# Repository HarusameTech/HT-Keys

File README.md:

# HT-Keys Public Repository

本リポジトリでは、_HT-Keys_ のファームウェアと開発者向け情報を公開しています

# HT-Keys とは

私 [Harusame](https://twitter.com/HarusameTech) が設計・制作している自作キーボードシリーズです

site：<https://www.harusame.tech/product/keyboard/HT-Keys/>  
購入
- HT-Keys-TKL
  - <https://harusametech.booth.pm/items/4568322>

# 製品シリーズ

## TKL

概要

- US 配列テンキーレス（87 キー）
- USB Type-C インターフェース採用
- CherryMX プロファイル
- RP2040 搭載 Raspberry Pi Pico 互換仕様
- ファームウェアレベルでカスタマイズ可能

## TK

概要

- 独自配列テンキー
- USB Type-C インターフェース採用
- CherryMX プロファイル
- RP2040 搭載 AE-RP2040 使用
- ファームウェアレベルでカスタマイズ可能

# Releases について

本リポジトリでは、以下のような命名規則を使用しています

| Releases の名前 | 意味 |
|:----|:----|
| `Developer Release` | HT-Keys のデバッグや開発用。主に開発者向け |
| `User Release - beta` | HT-Keys の開発段階のファームウェア。主に開発者向け |
| `User Release - Stable` | HT-Keys のファームウェア。使用者向け |

※ファームウェア開発を行うにあたり、何かしらのバグの解消ができたものを `beta` とし、開発時点で見つかっているバグをおおよそ、あるいは全て解消できたものを `Stable` としています

# ご使用の際の注意事項

本キーボードは US 配列です。そのため、Windows のキーボード設定を以下のように変更する必要があります

[設定] -> [言語と時刻] -> [言語] -> [優先する言語] の「オプション」から、ハードウェアキーボードレイアウトを変更してください

<div align="center"></div>
<div align="center">↓</div>
<div align="center"></div>
<div align="center">↓</div>
<div align="center"></div>

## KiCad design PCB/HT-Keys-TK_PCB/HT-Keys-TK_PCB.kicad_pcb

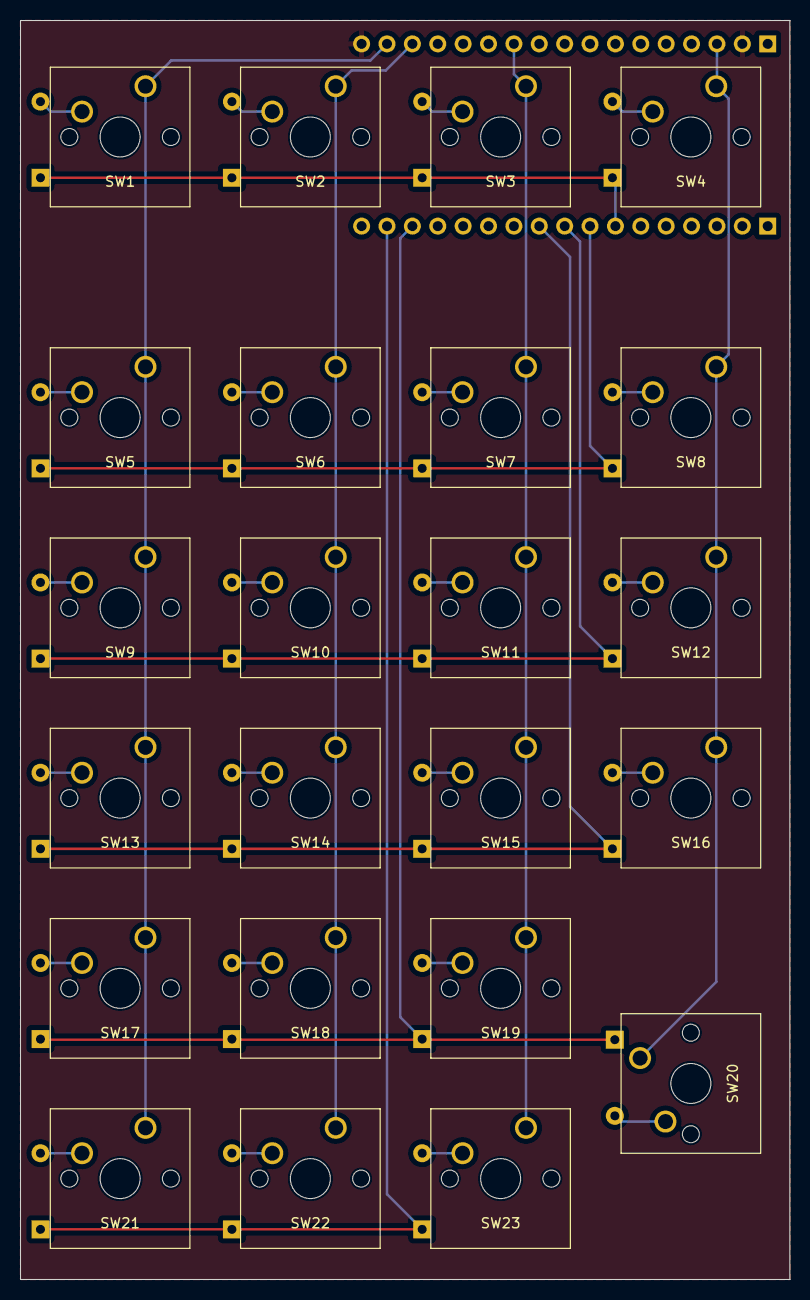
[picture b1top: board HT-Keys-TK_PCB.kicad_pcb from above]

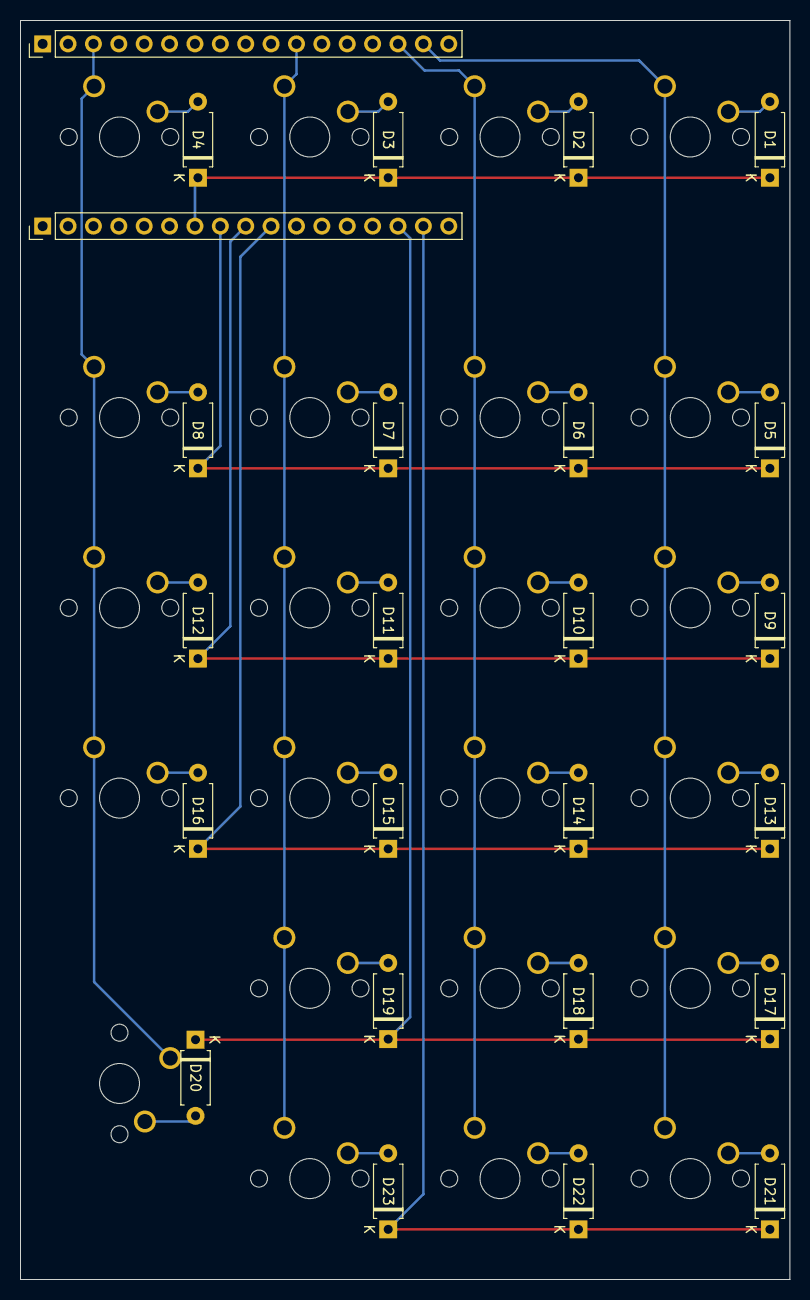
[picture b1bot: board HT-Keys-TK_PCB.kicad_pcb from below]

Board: 2 copper layers, 77.0 x 126.0 mm, 48 parts (25 on the bottom side), 34 nets.

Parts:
D1, D2, D3, D4, D5, D6, D7, D8, D9, D10, D11, D12, D13, D14, D15, D16, D17, D18, D19, D20, D21, D22, D23: D; D_A-405_P7.62mm_Horizontal
J1, J2: Conn_01x17_Pin; PinHeader_1x17_P2.54mm_Vertical
SW1, SW2, SW3, SW4, SW5, SW6, SW7, SW8, SW9, SW10, SW11, SW12, SW13, SW14, SW15, SW16, SW17, SW18, SW19, SW21, SW22, SW23: SW_Push; SW_Cherry_MX_1.00u_PCB
SW20: SW_Push; SW_Cherry_MX_2.00u_PCB

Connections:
GND: J2.2, J2.17
unnamed: D1.2 (A), SW1.2
unnamed: D2.2 (A), SW2.2
unnamed: D3.2 (A), SW3.2
unnamed: D4.2 (A), SW4.2
unnamed: D5.2 (A), SW5.2
unnamed: D6.2 (A), SW6.2
unnamed: D7.2 (A), SW7.2
unnamed: D8.2 (A), SW8.2
unnamed: D9.2 (A), SW9.2
unnamed: D10.2 (A), SW10.2
unnamed: D11.2 (A), SW11.2
unnamed: D12.2 (A), SW12.2
unnamed: D13.2 (A), SW13.2
unnamed: D14.2 (A), SW14.2
unnamed: D15.2 (A), SW15.2
unnamed: D16.2 (A), SW16.2
unnamed: D17.2 (A), SW17.2
unnamed: D18.2 (A), SW18.2
unnamed: D19.2 (A), SW19.2
unnamed: D20.2 (A), SW20.2
unnamed: D21.2 (A), SW21.2
unnamed: D22.2 (A), SW22.2
unnamed: D23.2 (A), SW23.2
Read0: J2.16, SW1.1, SW5.1, SW9.1, SW13.1, SW17.1, SW21.1
Read1: J2.15, SW2.1, SW6.1, SW10.1, SW14.1, SW18.1, SW22.1
Read2: J2.11, SW3.1, SW7.1, SW11.1, SW15.1, SW19.1, SW23.1
Read3: J2.3, SW4.1, SW8.1, SW12.1, SW16.1, SW20.1
Scan0: D1.1 (K), D2.1 (K), D3.1 (K), D4.1 (K), J1.7
Scan1: D5.1 (K), D6.1 (K), D7.1 (K), D8.1 (K), J1.8
Scan2: D9.1 (K), D10.1 (K), D11.1 (K), D12.1 (K), J1.9
Scan3: D13.1 (K), D14.1 (K), D15.1 (K), D16.1 (K), J1.10
Scan4: D17.1 (K), D18.1 (K), D19.1 (K), D20.1 (K), J1.15
Scan5: D21.1 (K), D22.1 (K), D23.1 (K), J1.16

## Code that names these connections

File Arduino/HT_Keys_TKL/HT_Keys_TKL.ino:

/* NOTE
 * If a compile error occurs,
 * Use "Raspberry Pi Pico/RP2040" by Earle F.Philhower
 * instead of "Arduino Mbed OS RP2040 Boards" by Arduino
 */


#include <Keyboard.h>
#define US_KEYBOARD

// キーマトリクスの処理の有効無効を指定:
// #define DEBUG_Matrix

// 実行速度モニタリングの有効無効を指定:
// #define DEBUG_Times

// キー出力を無効にする:
// #define DISABLE_KEYOUT

#ifdef DEBUG_Times
 #ifndef DEBUG
  #define DEBUG
 #endif
#endif

#ifdef DEBUG_Matrix
 #ifndef DEBUG
  #define DEBUG
 #endif
#endif

/* キー出力モードの指定用 */
#define MODE_Press true
#define MODE_Release false

/* 使用するGPIOを定義 */
#define Scan0 25
#define Scan1 20
#define Scan2 19
#define Scan3 18
#define Scan4 17
#define Scan5 16

#define Read0   0
#define Read1   1
#define Read2   2
#define Read3   3
#define Read4   4
#define Read5   5
#define Read6   6
#define Read7   7
#define Read8   8
#define Read9   9
#define Read10 10
#define Read11 11
#define Read12 12
#define Read13 13
#define Read14 21
#define Read15 23
#define Read16 24

/* 各キースイッチとそれに割り当てるキーの対応を定義 */
#define SW1  Key_ESC
#define SW2  Key_F1
#define SW3  Key_F2
#define SW4  Key_F3
#define SW5  Key_F4
#define SW6  Key_F5
#define SW7  Key_F6
#define SW8  Key_F7
#define SW9  Key_F8
#define SW10 Key_F9
#define SW11 Key_F10
#define SW12 Key_F11
#define SW13 Key_F12
#define SW14 Key_PrintScrn
#define SW15 Key_ScrollLock
#define SW16 Key_Pause
#define SW17 Key_Tilde
#define SW18 Key_1
#define SW19 Key_2
#define SW20 Key_3
#define SW21 Key_4
#define SW22 Key_5
#define SW23 Key_6
#define SW24 Key_7
#define SW25 Key_8
#define SW26 Key_9
#define SW27 Key_0
#define SW28 Key_Hyphen
#define SW29 Key_Equal
#define SW30 Key_Backspace
#define SW31 Key_Insert
#define SW32 Key_Home
#define SW33 Key_PageUp
#define SW34 Key_Tab
#define SW35 Key_Q
#define SW36 Key_W
#define SW37 Key_E
#define SW38 Key_R
#define SW39 Key_T
#define SW40 Key_Y
#define SW41 Key_U
#define SW42 Key_I
#define SW43 Key_O
#define SW44 Key_P
#define SW45 Key_L_Bracket
#define SW46 Key_R_Bracket
#define SW47 Key_BackSlash
#define SW48 Key_Delete
#define SW49 Key_End
#define SW50 Key_PageDown
#define SW51 Key_CapsLock
#define SW52 Key_A
#define SW53 Key_S
#define SW54 Key_D
#define SW55 Key_F
#define SW56 Key_G
#define SW57 Key_H
#define SW58 Key_J
#define SW59 Key_K
#define SW60 Key_L
#define SW61 Key_SemiColon
#define SW62 Key_Quote
#define SW63 Key_Enter
#define SW64 Key_L_Shift
#define SW65 Key_Z
#define SW66 Key_X
#define SW67 Key_C
#define SW68 Key_V
#define SW69 Key_B
#define SW70 Key_N
#define SW71 Key_M
#define SW72 Key_camma
#define SW73 Key_period
#define SW74 Key_slash
#define SW75 Key_R_Shift
#define SW76 Key_UP
#define SW77 Key_L_Ctrl
#define SW78 Key_L_Win
#define SW79 Key_L_Alt
#define SW80 Key_Space
#define SW81 Key_R_Alt
#define SW82 Key_R_Win
#define SW83 Key_App
#define SW84 Key_R_Ctrl
#define SW85 Key_LT
#define SW86 Key_DN
#define SW87 Key_RT


/* キー名称とキーコードの対応を定義 */
#define Null            0x00
#define Key_ESC         0xB1
#define Key_F1          0xC2
#define Key_F2          0xC3
#define Key_F3          0xC4
#define Key_F4          0xC5
#define Key_F5          0xC6
#define Key_F6          0xC7
#define Key_F7          0xC8
#define Key_F8          0xC9
#define Key_F9          0xCA
#define Key_F10         0xCB
#define Key_F11         0xCC
#define Key_F12         0xCD
#define Key_PrintScrn   0xCE
#define Key_ScrollLock  0xCF
#define Key_Pause       0xD0
#define Key_Tilde       0x60
#define Key_1           0x31
#define Key_2           0x32
#define Key_3           0x33
#define Key_4           0x34
#define Key_5           0x35
#define Key_6           0x36
#define Key_7           0x37
#define Key_8           0x38
#define Key_9           0x39
#define Key_0           0x30
#define Key_Hyphen      0x2D
#define Key_Equal       0x3D
#define Key_Backspace   0xB2
#define Key_Insert      0xD1
#define Key_Home        0xD2
#define Key_PageUp      0xD3
#define Key_Tab         0xB3
#define Key_Q           0x71
#define Key_W           0x77
#define Key_E           0x65
#define Key_R           0x72
#define Key_T           0x74
#define Key_Y           0x79
#define Key_U           0x75
#define Key_I           0x69
#define Key_O           0x6F
#define Key_P           0x70
#define Key_L_Bracket   0x5B
#define Key_R_Bracket   0x5D
#define Key_BackSlash   0x5C
#define Key_Delete      0xD4
#define Key_End         0xD5
#define Key_PageDown    0xD6
#define Key_CapsLock    0xC1
#define Key_A           0x61
#define Key_S           0x73
#define Key_D           0x64
#define Key_F           0x66
#define Key_G           0x67
#define Key_H           0x68
#define Key_J           0x6A
#define Key_K           0x6B
#define Key_L           0x6C
#define Key_SemiColon   0x3B
#define Key_Quote       0x27
#define Key_Enter       0xB0
#define Key_L_Shift     0x81
#define Key_Z           0x7A
#define Key_X           0x78
#define Key_C           0x63
#define Key_V           0x76
#define Key_B           0x62
#define Key_N           0x6E
#define Key_M           0x6D
#define Key_camma       0x2C
#define Key_period      0x2E
#define Key_slash       0x2F
#define Key_R_Shift     0x85
#define Key_UP          0xDA
#define Key_L_Ctrl      0x80
#define Key_L_Win       0x83
#define Key_L_Alt       0x82
#define Key_Space       0x20
#define Key_R_Alt       0x86
#define Key_R_Win       0x87
#define Key_App         0xED
#define Key_R_Ctrl      0x84
#define Key_LT          0xD8
#define Key_DN          0xD9
#define Key_RT          0xD7

/* GPIO初期化用配列 */
const uint8_t Scan[] = {Scan0, Scan1, Scan2, Scan3, Scan4, Scan5 };
const uint8_t Read[] = {Read0, Read1, Read2, Read3, Read4, Read5, Read6, Read7, Read8, Read9, Read10, Read11, Read12, Read13, Read14, Read15, Read16};

/* キーマトリクス操作用配列 */
const uint8_t keyMap[sizeof(Scan)][sizeof(Read)] = {
  {SW1 , Null, SW2 , SW3 , SW4 , SW5 , SW6 , SW7 , SW8 , SW9 , SW10, SW11, SW12, SW13, SW14, SW15, SW16},
  {SW17, SW18, SW19, SW20, SW21, SW22, SW23, SW24, SW25, SW26, SW27, SW28, SW29, SW30, SW31, SW32, SW33},
  {SW34, SW35, SW36, SW37, SW38, SW39, SW40, SW41, SW42, SW43, SW44, SW45, SW46, SW47, SW48, SW49, SW50},
  {SW51, SW52, SW53, SW54, SW55, SW56, SW57, SW58, SW59, SW60, SW61, SW62, Null, SW63, Null, Null, Null},
  {SW64, SW65, SW66, SW67, SW68, SW69, SW70, SW71, SW72, SW73, SW74, Null, Null, SW75, Null, SW76, Null},
  {SW77, SW78, SW79, Null, Null, SW80, Null, Null, Null, SW81, SW82, SW83, Null, SW84, SW85, SW86, SW87}};

/* キーマトリクスの状態保存用配列 */
volatile uint8_t Matrix[sizeof(Scan)][sizeof(Read)];

void setup() {
#ifdef DEBUG
  /* デバッグ用シリアル通信を115200bpsで開始 */
  Serial.begin(115200);
#endif

  /* 読み取り線を入力にしてプルアップ */
  for(uint8_t i = 0; i < sizeof(Read); i++) {
    pinMode(Read[i], INPUT_PULLUP);
  }

  /* スキャン線を出力にしてすべてHIGH */
  for(uint8_t i = 0; i < sizeof(Scan); i++) {
    pinMode(Scan[i], OUTPUT);
    digitalWrite(Scan[i], HIGH);
  }
 
#ifndef DISABLE_KEYOUT
  /* キーボードエミュレート開始 */
  Keyboard.begin();
#endif
}

void loop() {
  readKeyPad();  // キーボードの状態を読み取り、配列を更新する:
  checkMatrix();  // 配列を参照し押されたかどうかを判断:

  delayMicroseconds(4000);
}

void readKeyPad(void) {
  for(uint8_t i = 0; i < sizeof(Scan); i++) {     // スキャン線を順に切り替え:
    digitalWrite(Scan[i], LOW);                   // 読み取るところだけ落とす:
    delayMicroseconds(8);                         // ゴースト発生防止:
    for(uint8_t o = 0; o < sizeof(Read); o++) {   // 読み取って配列を更新:
      Matrix[i][o] = (Matrix[i][o] << 1) + (digitalRead(Read[o]) ? 0 : 1);
      delayMicroseconds(8);                       // ゴースト発生防止:
    }
    digitalWrite(Scan[i], HIGH);                  // 定常状態に戻す:
  }

#ifdef DEBUG_Matrix
  /* デバッグ表示 */
  for(uint8_t i = 0; i < sizeof(Scan); i++) {
    Serial.print(" | ");
    for(uint8_t o = 0; o < sizeof(Read); o++) {
      for(uint8_t b = 7; b > 0; b--) {            // 配列のデータを MSB から選択:
        if((Matrix[i][o] & 1 << b) == 0) {        // 配列のデータの対応するビットが 0 かどうかを判定:
          Serial.print("0");
        }else {
          Serial.print("1");
        }
      }
      Serial.print(" | ");
    }
    Serial.print("\n");
  }
  Serial.print("\n");
#endif
}

void checkMatrix(void) {
  /* キーボード出力 */
  for(uint8_t i = 0; i < sizeof(Scan); i++) {
    for(uint8_t o = 0; o < sizeof(Read); o++) {
      if((Matrix[i][o] & 0b00001111) == 0b00000011) {
        keyOut(keyMap[i][o], MODE_Press);
      }else if((Matrix[i][o] & 0b00000111) == 0b00000100) {
        keyOut(keyMap[i][o], MODE_Release);
      }
    }
  }
}

void keyOut(const uint8_t key, const bool mode) {
#ifndef DISABLE_KEYOUT
  if(key == 0) {
  }else {
    if(mode) {
      Keyboard.press(key);
    }else {
      Keyboard.release(key);
    }
  }
#endif
}

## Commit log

2023-03-06 Update HT_Keys_TKL.ino
    バックスラッシュキー以外のキーコードの特定が完了
2023-03-07 Update HT_Keys_TKL.ino
    US 配列を明示するように変更
    大文字が入力されていたので小文字になるように `0x20` を引くように変更
    バージョン番号をコード内に追加
2023-03-09 Add files via upload
    回路図の PDF ファイルを追加
2023-05-05 fix fqbn
2023-05-05 fix path
2023-05-06 fix build.yaml
2023-05-06 edit build.yaml
2023-07-07 シフトキーのキーコードを修正
2023-07-08 シフトキーを入れ替え
2023-07-15 不要なルーチンを削除
2023-07-15 キーリリースの判断条件を変更
2023-07-15 入れ替えてたシフトキーを戻した
2023-07-15 キーリリースの条件変更
2023-07-15 割り当てる文字コードを間違えていたので修正
2023-09-14 v2 のファイルを作成
2023-09-14 動作見直し
2023-09-15 コードを整形
2023-09-16 コメントを追加
2023-09-17 コメントを編集
2023-09-21 add booth link
2023-09-27 HT-Keys-TK 基板 v1
2023-09-27 HT_Keys_TK PCB v1
2023-09-29 add schematic pdf
2024-02-29 Rename HT-Keys-TKL_Schematic.pdf to schematic/HT-Keys-TKL_Schematic.pdf
2024-05-07 ステータス表示を追加
2024-05-07 ピンアサイン更新
2024-05-24 udapte
